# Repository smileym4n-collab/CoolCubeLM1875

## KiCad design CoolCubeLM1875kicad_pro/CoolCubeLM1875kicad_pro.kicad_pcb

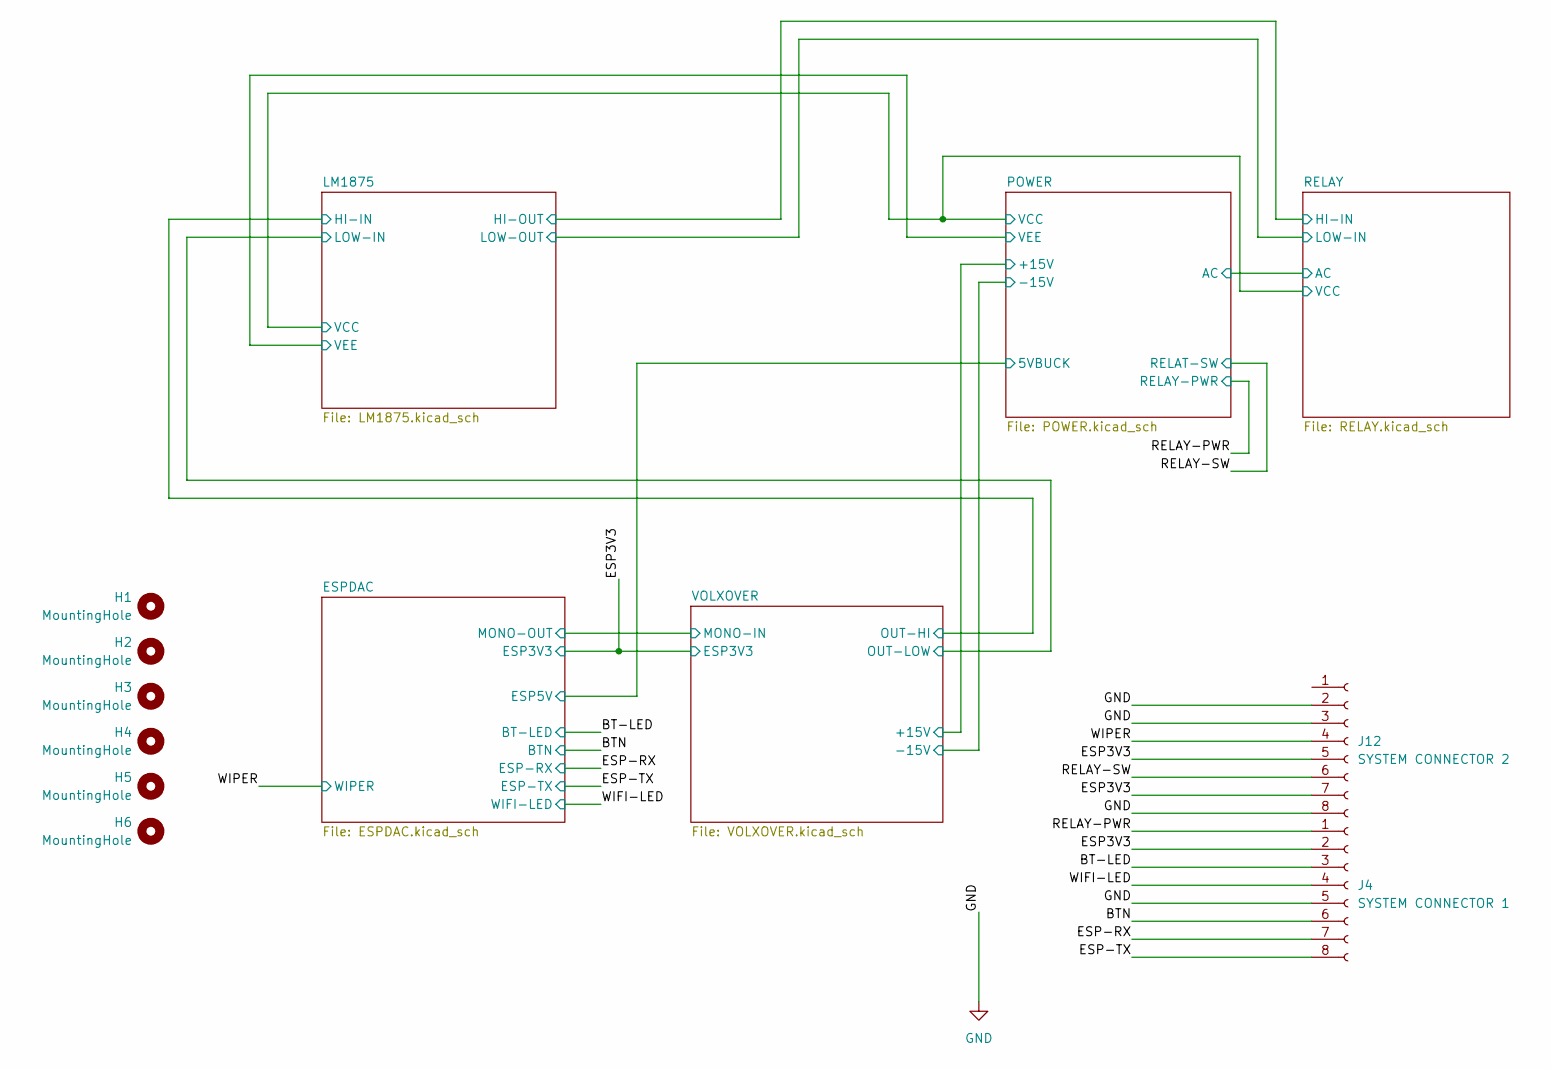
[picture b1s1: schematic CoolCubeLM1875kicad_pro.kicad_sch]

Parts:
H1, H2, H3, H4, H5, H6: MountingHole; MountingHole_4mm
J4: SYSTEM CONNECTOR 1; JST_XH_B8B-XH-A_1x08_P2.50mm_Vertical
J12: SYSTEM CONNECTOR 2; JST_XH_B8B-XH-A_1x08_P2.50mm_Vertical

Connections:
/BT-LED: J4.3; also elsewhere on the board
/BTN: J4.6; also elsewhere on the board
/ESP3V3: J4.2, J12.5, J12.7; also elsewhere on the board
/ESP-RX: J4.7; also elsewhere on the board
/ESP-TX: J4.8; also elsewhere on the board
/RELAY-PWR: J4.1; also elsewhere on the board
/RELAY-SW: J12.6; also elsewhere on the board
/WIFI-LED: J4.4; also elsewhere on the board
/WIPER: J12.4; also elsewhere on the board
GND: J4.5, J12.2, J12.3, J12.8; also elsewhere on the board

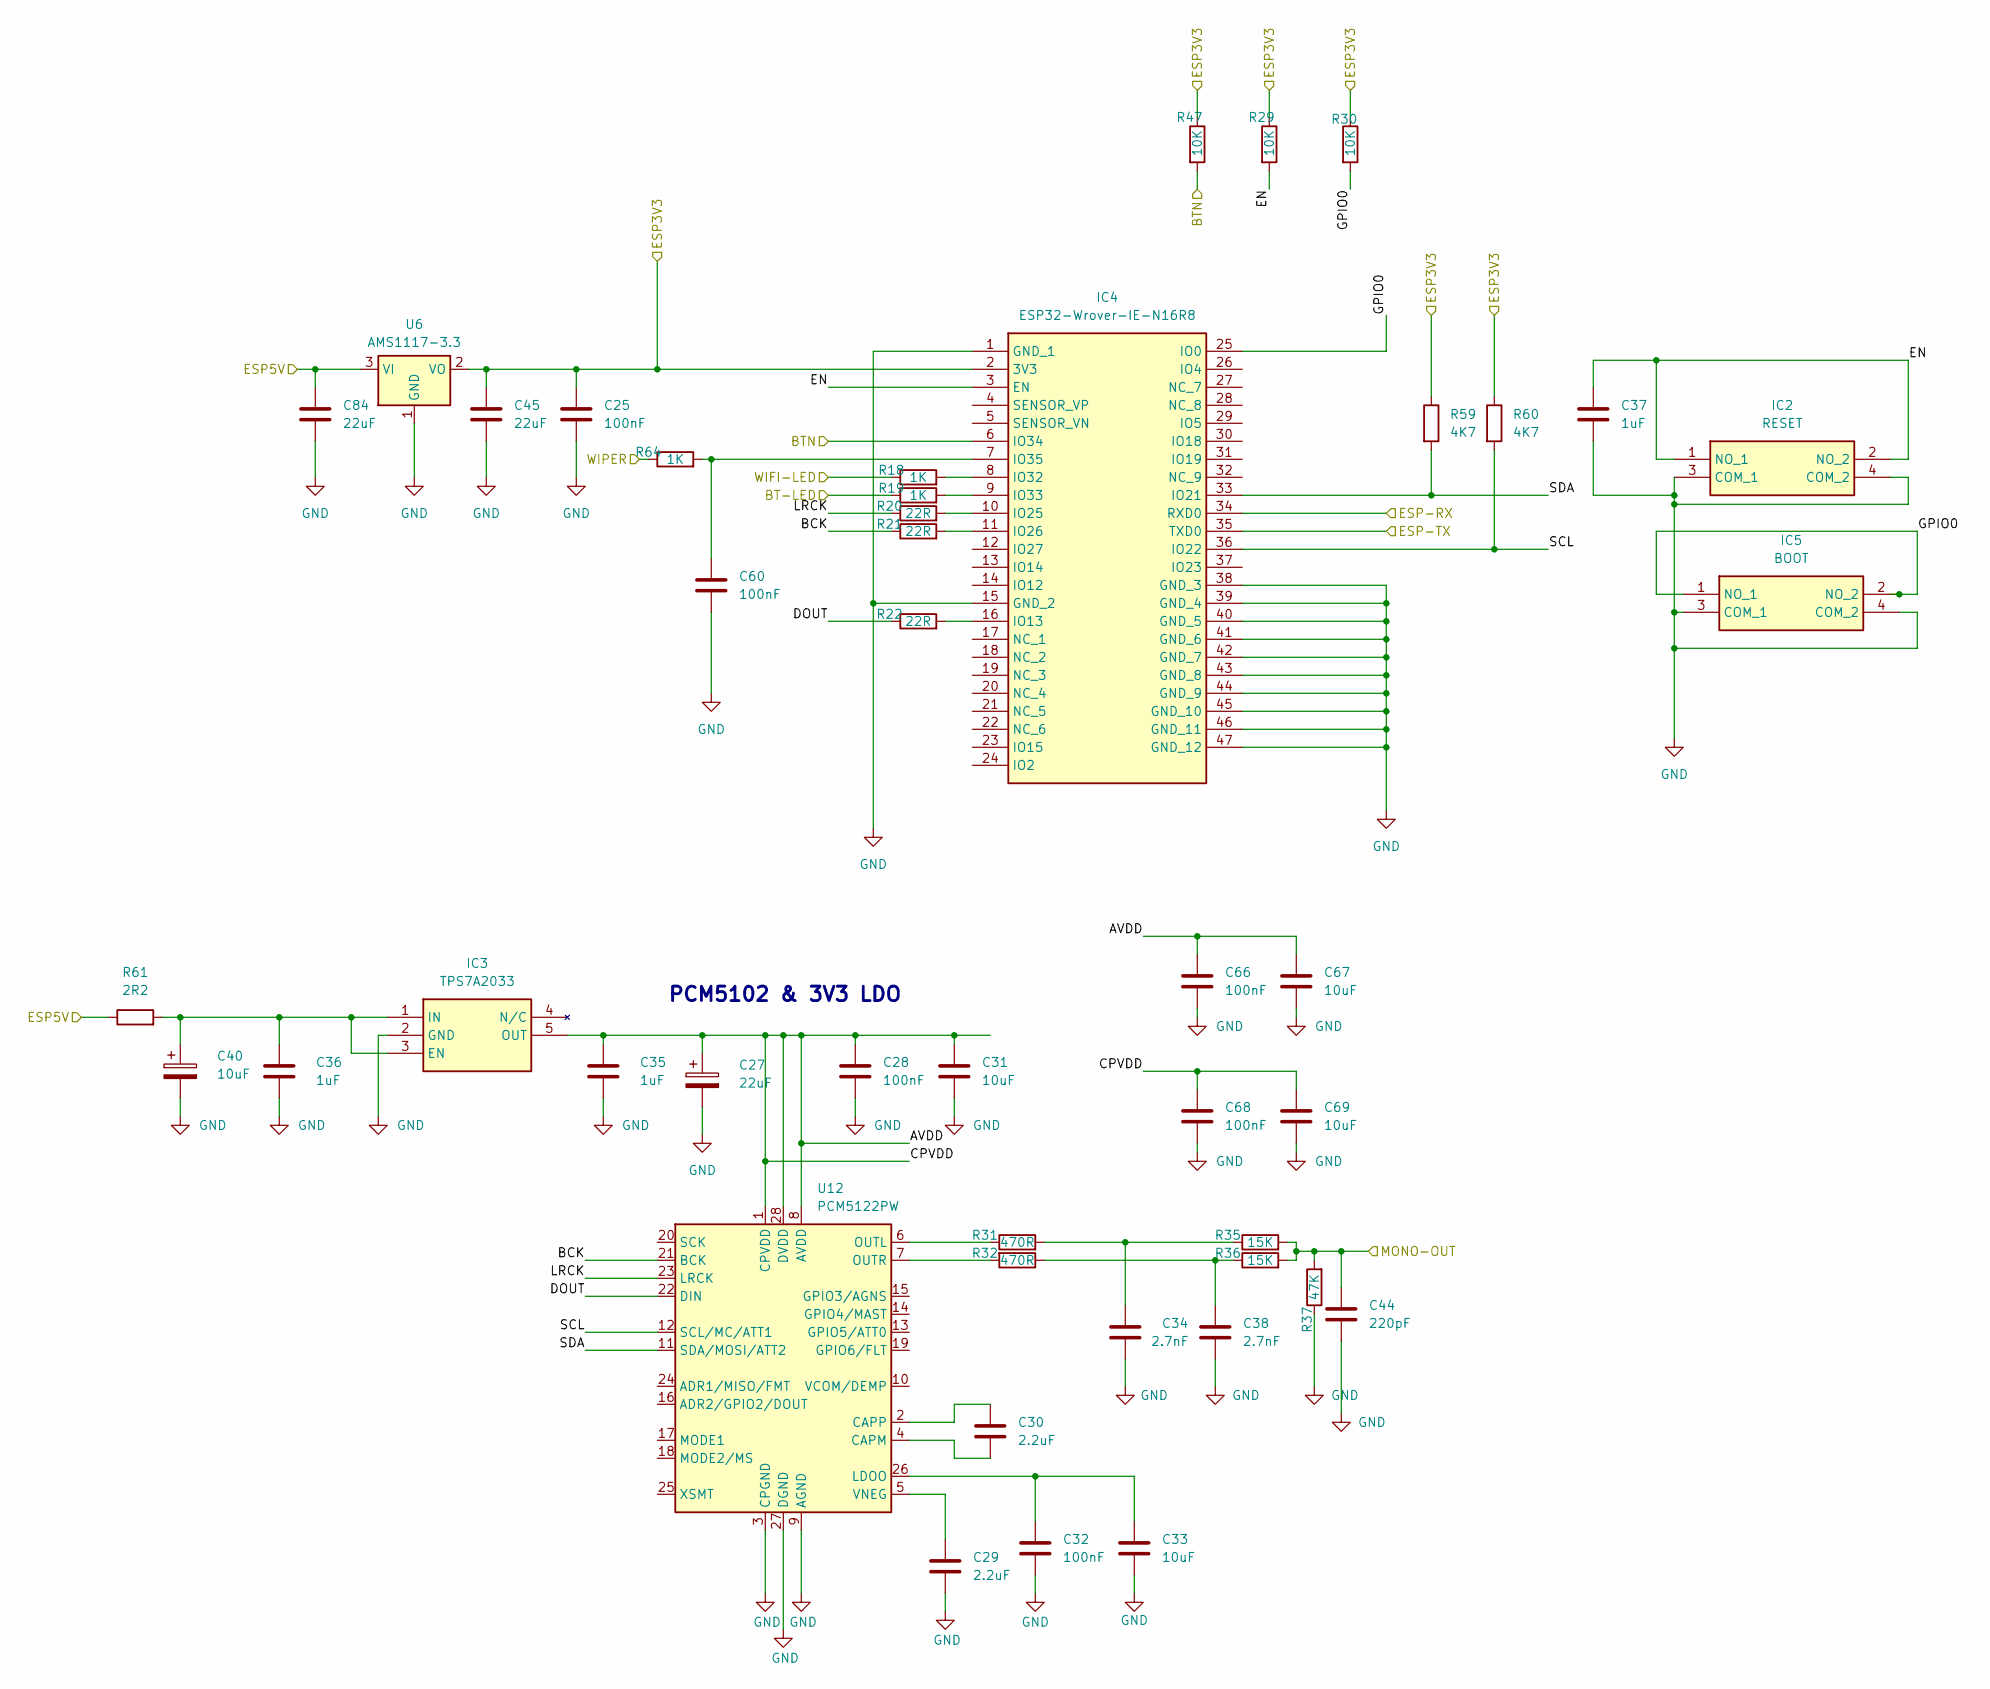
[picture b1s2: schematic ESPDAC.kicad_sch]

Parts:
C25, C28, C32, C60, C66, C68: 100nF; C_1206_3216Metric_Pad1.33x1.80mm_HandSolder
C27: 22uF; CP_Radial_D5.0mm_P2.50mm
C29, C30: 2.2uF; C_0805_2012Metric_Pad1.18x1.45mm_HandSolder
C31, C67, C69: 10uF; C_0805_2012Metric_Pad1.18x1.45mm_HandSolder
C33: 10uF; C_1206_3216Metric_Pad1.33x1.80mm_HandSolder
C34, C38: 2.7nF; C_0805_2012Metric_Pad1.18x1.45mm_HandSolder
C35, C36, C37: 1uF; C_1206_3216Metric_Pad1.33x1.80mm_HandSolder
C40: 10uF; CP_Radial_D4.0mm_P1.50mm
C44: 220pF; C_0603_1608Metric_Pad1.08x0.95mm_HandSolder
C45, C84: 22uF; C_0805_2012Metric_Pad1.18x1.45mm_HandSolder
IC2: RESET; TS026650BK100SCRD; Mouser Part Number 179-TS026650BK100SCR
IC3: TPS7A2033; SOT95P280X145-5N; Mouser Part Number 595-TPS7A2033PDBVR
IC4: ESP32-Wrover-IE-N16R8; ESP32-WROVER-IE-N16R8; Mouser Part Number 356-ESP32WRVIE2864UC
IC5: BOOT; TS026650BK100SCRD; Mouser Part Number 179-TS026650BK100SCR
R18, R19, R64: 1K; R_0805_2012Metric_Pad1.20x1.40mm_HandSolder
R20, R21, R22: 22R; R_0603_1608Metric_Pad0.98x0.95mm_HandSolder
R29, R30, R47: 10K; R_0603_1608Metric_Pad0.98x0.95mm_HandSolder
R31, R32: 470R; R_0805_2012Metric_Pad1.20x1.40mm_HandSolder
R35, R36: 15K; R_0805_2012Metric_Pad1.20x1.40mm_HandSolder
R37: 47K; R_0805_2012Metric_Pad1.20x1.40mm_HandSolder
R59, R60: 4K7; R_0805_2012Metric_Pad1.20x1.40mm_HandSolder
R61: 2R2; R_0805_2012Metric_Pad1.20x1.40mm_HandSolder
U6: AMS1117-3.3; SOT-223-3_TabPin2
U12: PCM5122PW; TSSOP-28_4.4x9.7mm_P0.65mm

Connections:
/BT-LED: R19.1; also elsewhere on the board
/BTN: IC4.6 (IO34), R47.2; also elsewhere on the board
/ESP3V3: C25.1, C45.1, IC4.2 (3V3), R29.1, R30.1, R47.1, R59.1, R60.1, U6.2 (VO); also elsewhere on the board
/ESP-RX: IC4.34 (RXD0); also elsewhere on the board
/ESP-TX: IC4.35 (TXD0); also elsewhere on the board
/ESPDAC/AVDD: C27.1, C28.1, C31.1, C35.1, C66.1, C67.1, C68.1, C69.1, IC3.5 (OUT), U12.1 (CPVDD), U12.8 (AVDD), U12.28 (DVDD)
/ESPDAC/BCK: R21.1, U12.21 (BCK)
/ESPDAC/DOUT: R22.1, U12.22 (DIN)
/ESPDAC/EN: C37.1, IC2.1 (NO_1), IC2.2 (NO_2), IC4.3 (EN), R29.2
/ESPDAC/ESP5V: C84.1, R61.1, U6.3 (VI); also elsewhere on the board
/ESPDAC/GPIO0: IC4.25 (IO0), IC5.1 (NO_1), IC5.2 (NO_2), R30.2
/ESPDAC/LRCK: R20.1, U12.23 (LRCK)
/ESPDAC/MONO-OUT: C44.1, R35.2, R36.2, R37.2; also elsewhere on the board
/ESPDAC/SCL: IC4.36 (IO22), R60.2, U12.12 (SCL/MC/ATT1)
/ESPDAC/SDA: IC4.33 (IO21), R59.2, U12.11 (SDA/MOSI/ATT2)
/WIFI-LED: R18.1; also elsewhere on the board
/WIPER: R64.1; also elsewhere on the board
GND: C25.2, C27.2, C28.2, C29.2, C31.2, C32.2, C33.2, C34.2, C35.2, C36.2, C37.2, C38.2, C40.2, C44.2, C45.2, C60.2, C66.2, C67.2, C68.2, C69.2, C84.2, IC2.3 (COM_1), IC2.4 (COM_2), IC3.2 (GND), IC4.1 (GND_1), IC4.15 (GND_2), IC4.38 (GND_3), IC4.39 (GND_4), IC4.40 (GND_5), IC4.41 (GND_6), IC4.42 (GND_7), IC4.43 (GND_8), IC4.44 (GND_9), IC4.45 (GND_10), IC4.46 (GND_11), IC4.47 (GND_12), IC5.3 (COM_1), IC5.4 (COM_2), R37.1, U6.1 (GND), U12.3 (CPGND), U12.9 (AGND), U12.27 (DGND); also elsewhere on the board
unnamed: C34.1, R31.2, R35.1
unnamed: C38.1, R32.1, R36.1
unnamed: C36.1, C40.1, IC3.1 (IN), IC3.3 (EN), R61.2
unnamed: IC4.16 (IO13), R22.2
unnamed: IC4.10 (IO25), R20.2
unnamed: IC4.11 (IO26), R21.2
unnamed: IC4.8 (IO32), R18.2
unnamed: IC4.9 (IO33), R19.2
unnamed: C60.1, IC4.7 (IO35), R64.2
unnamed: C30.2, U12.4 (CAPM)
unnamed: C30.1, U12.2 (CAPP)
unnamed: C32.1, C33.1, U12.26 (LDOO)
unnamed: R31.1, U12.6 (OUTL)
unnamed: R32.2, U12.7 (OUTR)
unnamed: C29.1, U12.5 (VNEG)

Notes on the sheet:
PCM5102 & 3V3 LDO

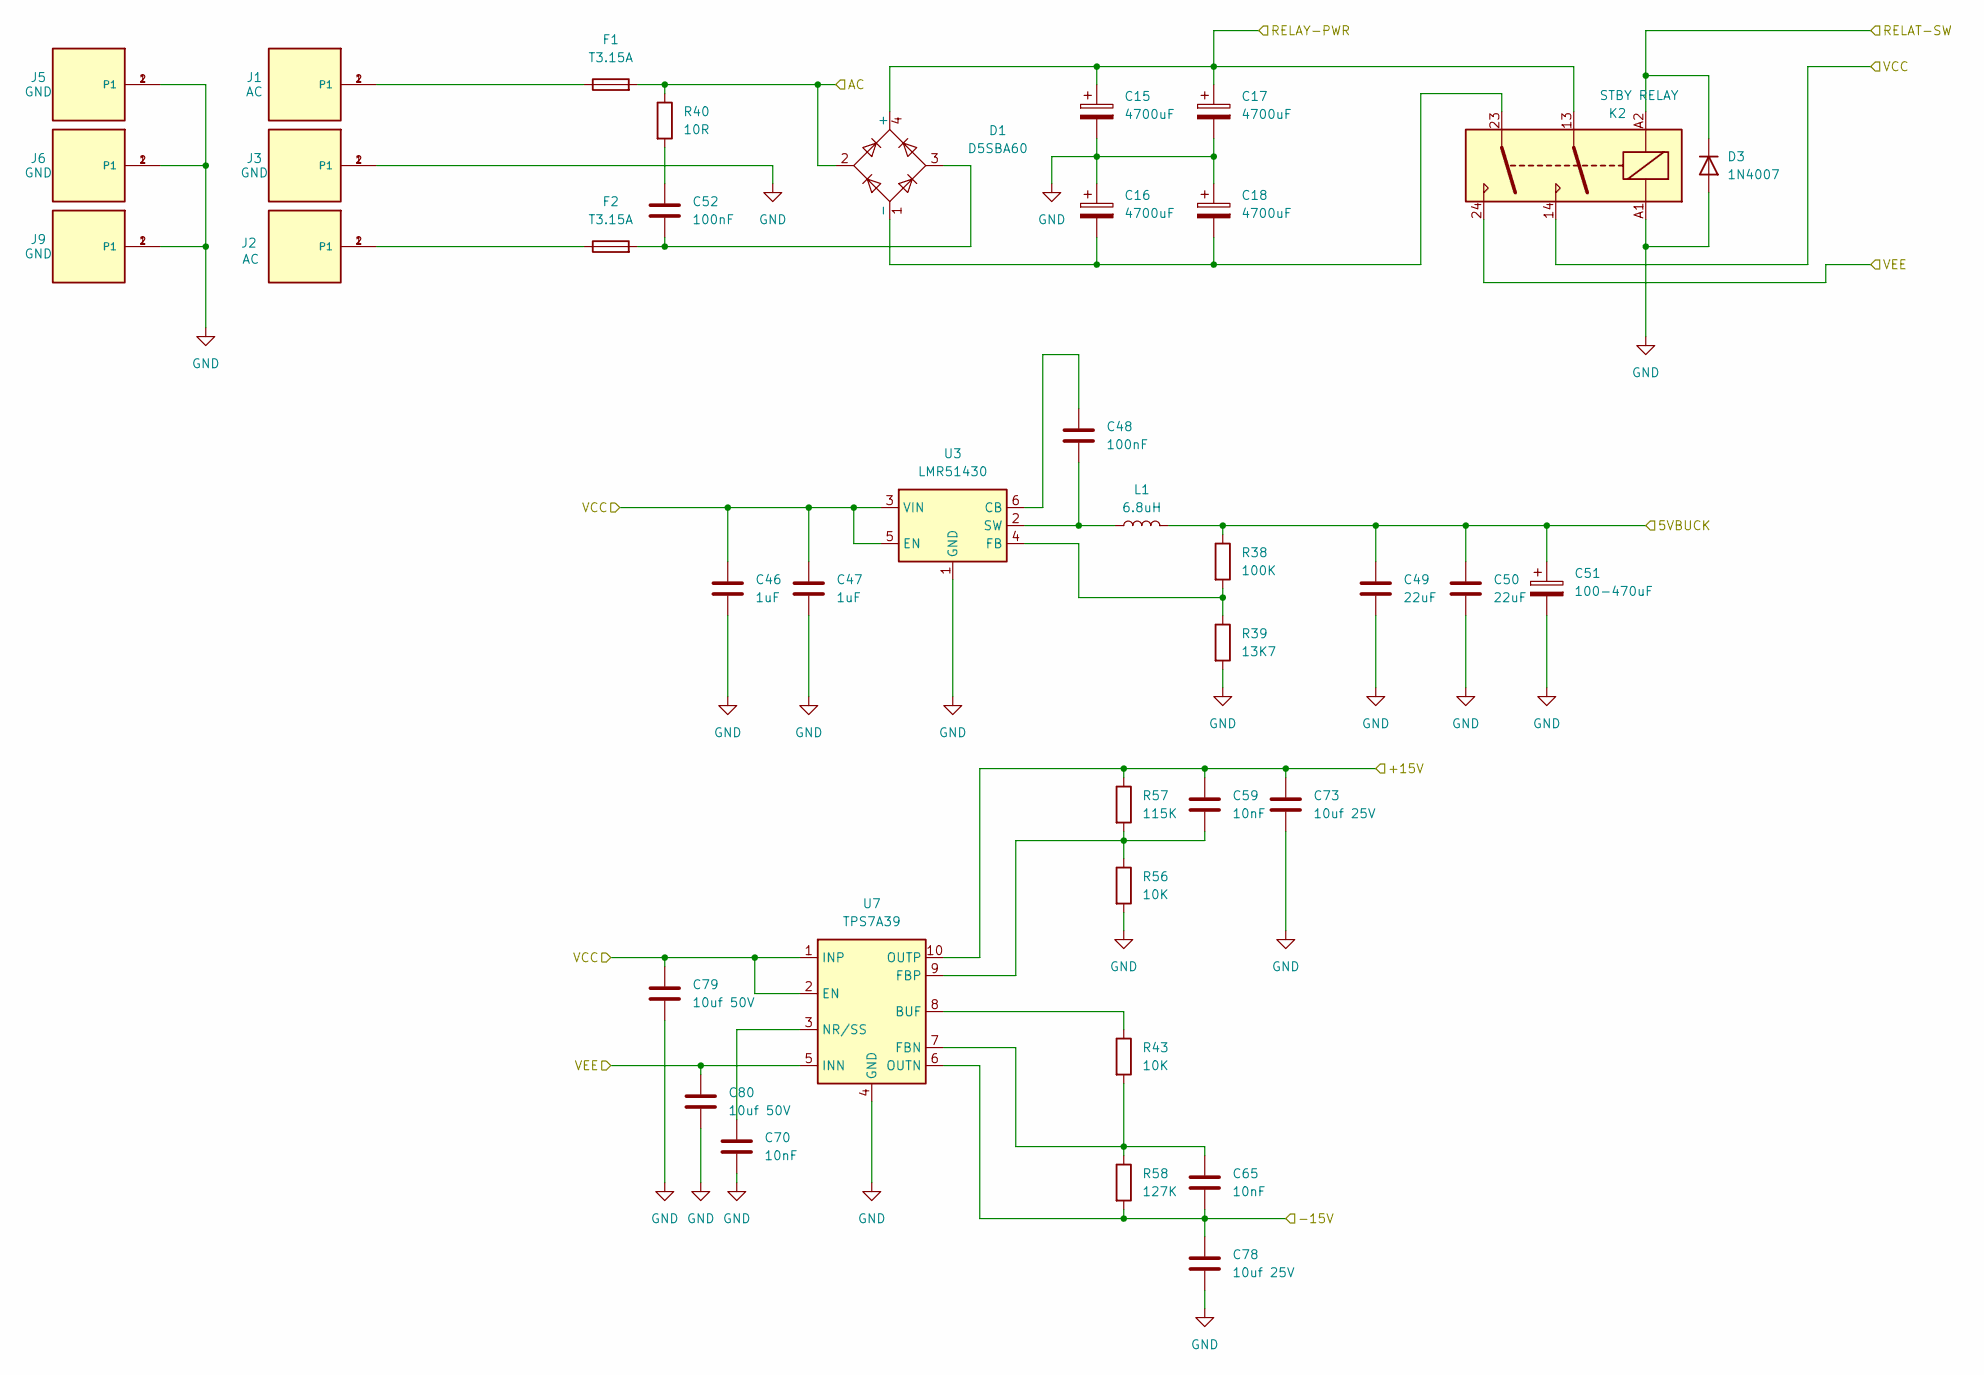
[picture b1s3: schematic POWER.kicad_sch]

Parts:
C15, C16, C17, C18: 4700uF; CP_Radial_D22.0mm_P10.00mm_SnapIn
C46, C47: 1uF; C_1206_3216Metric_Pad1.33x1.80mm_HandSolder
C48: 100nF; C_1206_3216Metric_Pad1.33x1.80mm_HandSolder
C49, C50: 22uF; C_1206_3216Metric_Pad1.33x1.80mm_HandSolder
C51: 100-470uF; CP_Radial_D8.0mm_P3.50mm
C52: 100nF; C_Rect_L18.0mm_W5.0mm_P15.00mm_FKS3_FKP3
C59, C65, C70: 10nF; C_0805_2012Metric_Pad1.18x1.45mm_HandSolder
C73, C78: 10uf 25V; C_1206_3216Metric_Pad1.33x1.80mm_HandSolder
C79, C80: 10uf 50V; C_1206_3216Metric_Pad1.33x1.80mm_HandSolder
D1: D5SBA60; Diode_Bridge_32.0x5.6x17.0mm_P10.0mm_P7.5mm
D3: 1N4007; D_DO-41_SOD81_P10.16mm_Horizontal
F1, F2: T3.15A; Fuseholder_Cylinder-5x20mm_Schurter_0031_8201_Horizontal_Op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
J1, J2: AC; TE_62409-1; PART_DESCRIPTION CONN QC TAB 0.250 SOLDER
J3, J5, J6, J9: GND; TE_62409-1; PART_DESCRIPTION CONN QC TAB 0.250 SOLDER
K2: STBY RELAY; Relay_DPST_Omron_G2RL-2A
L1: 6.8uH; SRP6030WA-6R8M
R38: 100K; R_0805_2012Metric_Pad1.20x1.40mm_HandSolder
R39: 13K7; R_0805_2012Metric_Pad1.20x1.40mm_HandSolder
R40: 10R; R_Axial_DIN0617_L17.0mm_D6.0mm_P20.32mm_Horizontal
R43, R56: 10K; R_0805_2012Metric_Pad1.20x1.40mm_HandSolder
R57: 115K; R_0805_2012Metric_Pad1.20x1.40mm_HandSolder
R58: 127K; R_0805_2012Metric_Pad1.20x1.40mm_HandSolder
U3: LMR51430; SOT-23-6_Handsoldering
U7: TPS7A39; Texas_S-PVSON-N10_ThermalVias

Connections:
/ESPDAC/ESP5V: C49.1, C50.1, C51.1, L1.2, R38.1; also elsewhere on the board
/LM1875/VCC: C46.1, C47.1, C79.1, K2.14, U3.3 (VIN), U3.5 (EN), U7.1 (INP), U7.2 (EN); also elsewhere on the board
/LM1875/VEE: C80.1, K2.24, U7.5 (INN); also elsewhere on the board
/POWER/+15V: C59.1, C73.1, R57.1, U7.10 (OUTP); also elsewhere on the board
/POWER/-15V: C65.2, C78.1, R58.2, U7.6 (OUTN); also elsewhere on the board
/POWER/AC: D1.2, F1.2, R40.1; also elsewhere on the board
/RELAY-PWR: C15.1, C17.1, D1.4 (+), K2.13; also elsewhere on the board
/RELAY-SW: D3.1 (K), K2.A2; also elsewhere on the board
GND: C15.2, C16.1, C17.2, C18.1, C46.2, C47.2, C49.2, C50.2, C51.2, C70.2, C73.2, C78.2, C79.2, C80.2, D3.2 (A), J3.1, J3.2 (P1), J5.1, J5.2 (P1), J6.1, J6.2 (P1), J9.1, J9.2 (P1), K2.A1, R39.2, R56.2, U3.1 (GND), U7.4 (GND), U7.11 (GND); also elsewhere on the board
unnamed: C52.1, R40.2
unnamed: C52.2, D1.3, F2.2
unnamed: C16.2, C18.2, D1.1 (-), K2.23
unnamed: F1.1, J1.1, J1.2 (P1)
unnamed: F2.1, J2.1, J2.2 (P1)
unnamed: C48.1, U3.6 (CB)
unnamed: R38.2, R39.1, U3.4 (FB)
unnamed: C48.2, L1.1, U3.2 (SW)
unnamed: R43.1, U7.8 (BUF)
unnamed: C65.1, R43.2, R58.1, U7.7 (FBN)
unnamed: C59.2, R56.1, R57.2, U7.9 (FBP)
unnamed: C70.1, U7.3 (NR/SS)

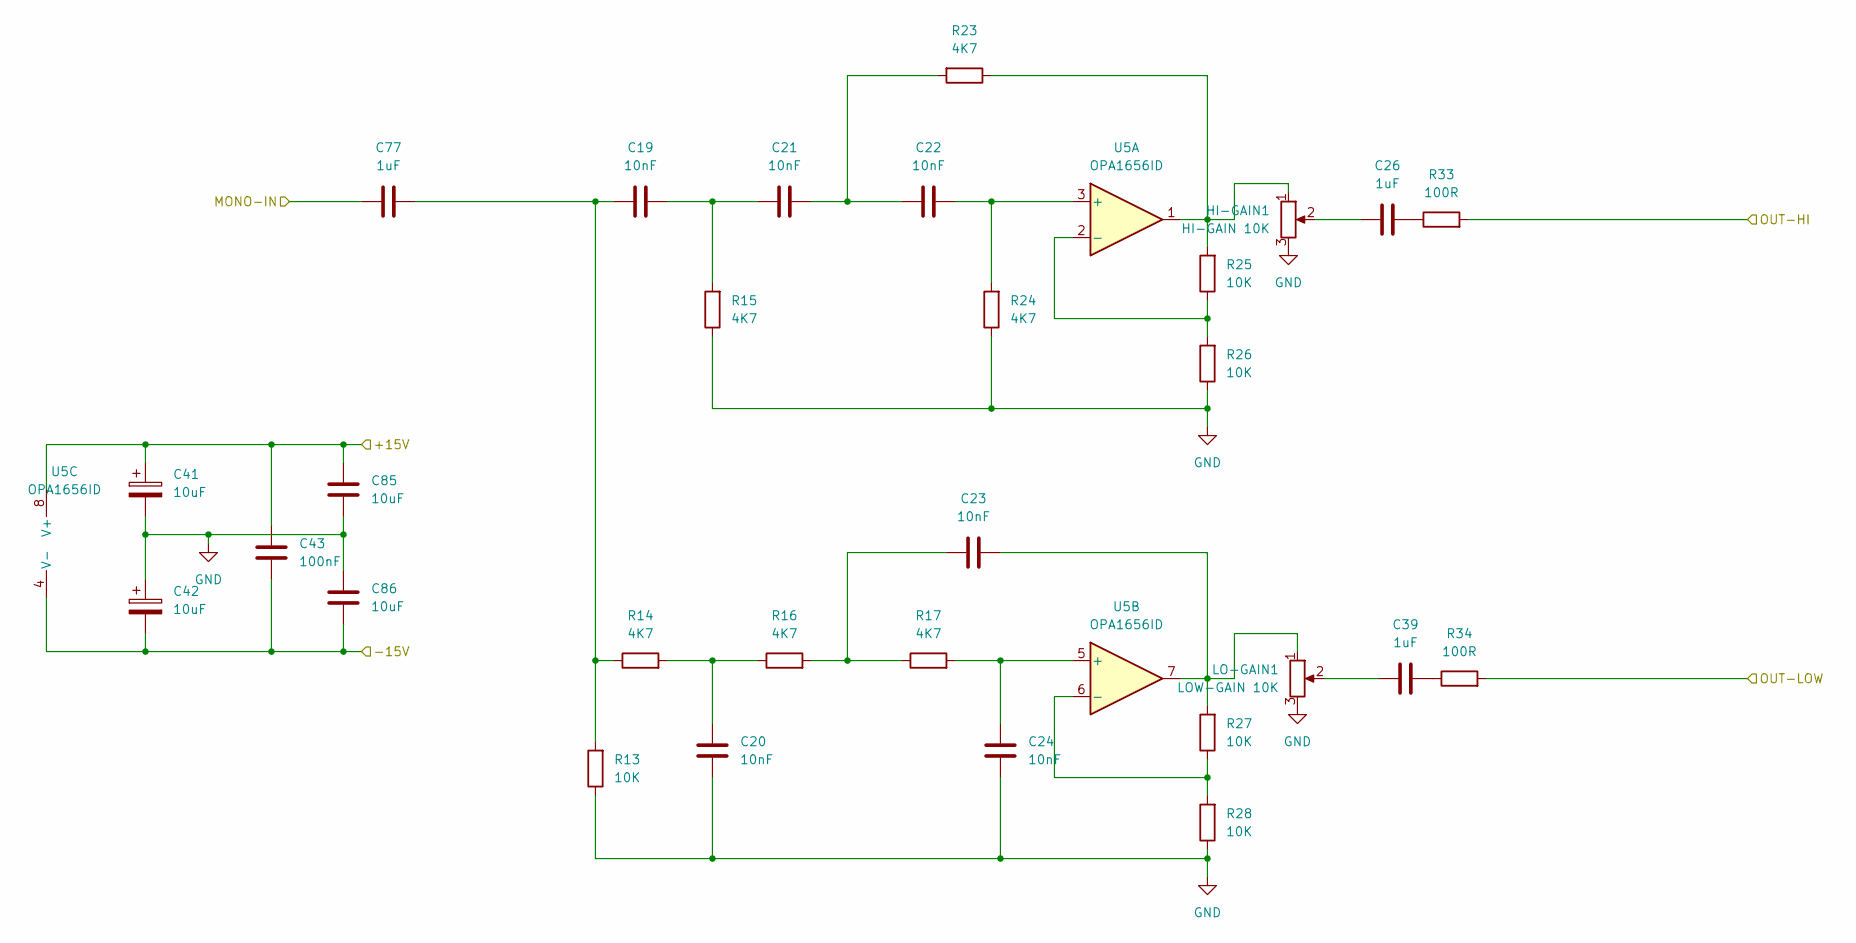
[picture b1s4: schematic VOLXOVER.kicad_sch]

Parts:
C19, C20, C21, C22, C23, C24: 10nF; C_0805_2012Metric_Pad1.18x1.45mm_HandSolder
C26, C39, C77: 1uF; C_Rect_L7.2mm_W5.5mm_P5.00mm_FKS2_FKP2_MKS2_MKP2
C41, C42: 10uF; CP_Radial_D5.0mm_P2.50mm
C43: 100nF; C_1206_3216Metric_Pad1.33x1.80mm_HandSolder
C85, C86: 10uF; C_1206_3216Metric_Pad1.33x1.80mm_HandSolder
HI-GAIN1: HI-GAIN 10K; Potentiometer_Vishay_T93YA_Vertical
LO-GAIN1: LOW-GAIN 10K; Potentiometer_Vishay_T93YA_Vertical
R13, R25, R26, R27, R28: 10K; R_0805_2012Metric_Pad1.20x1.40mm_HandSolder
R14, R15, R16, R17, R23, R24: 4K7; R_0805_2012Metric_Pad1.20x1.40mm_HandSolder
R33, R34: 100R; R_0805_2012Metric_Pad1.20x1.40mm_HandSolder
U5: OPA1656ID; SOIC-8_3.9x4.9mm_P1.27mm

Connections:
/ESPDAC/MONO-OUT: C77.1; also elsewhere on the board
/LM1875/HI-IN: R33.2; also elsewhere on the board
/LM1875/LOW-IN: R34.2; also elsewhere on the board
/POWER/+15V: C41.1, C43.1, C85.1, U5.8 (V+); also elsewhere on the board
/POWER/-15V: C42.2, C43.2, C86.2, U5.4 (V-); also elsewhere on the board
GND: C20.1, C24.1, C41.2, C42.1, C85.2, C86.1, HI-GAIN1.3, LO-GAIN1.3, R13.1, R15.1, R24.1, R26.1, R28.1; also elsewhere on the board
unnamed: C19.1, C77.2, R13.2, R14.1
unnamed: C19.2, C21.1, R15.2
unnamed: C20.2, R14.2, R16.1
unnamed: C21.2, C22.1, R23.2
unnamed: C23.1, R16.2, R17.1
unnamed: C23.2, LO-GAIN1.1, R27.2, U5.7
unnamed: C26.1, HI-GAIN1.2
unnamed: C26.2, R33.1
unnamed: C39.1, LO-GAIN1.2
unnamed: C39.2, R34.1
unnamed: HI-GAIN1.1, R23.1, R25.2, U5.1
unnamed: C22.2, R24.2, U5.3 (+)
unnamed: R25.1, R26.2, U5.2 (-)
unnamed: C24.2, R17.2, U5.5 (+)
unnamed: R27.1, R28.2, U5.6 (-)

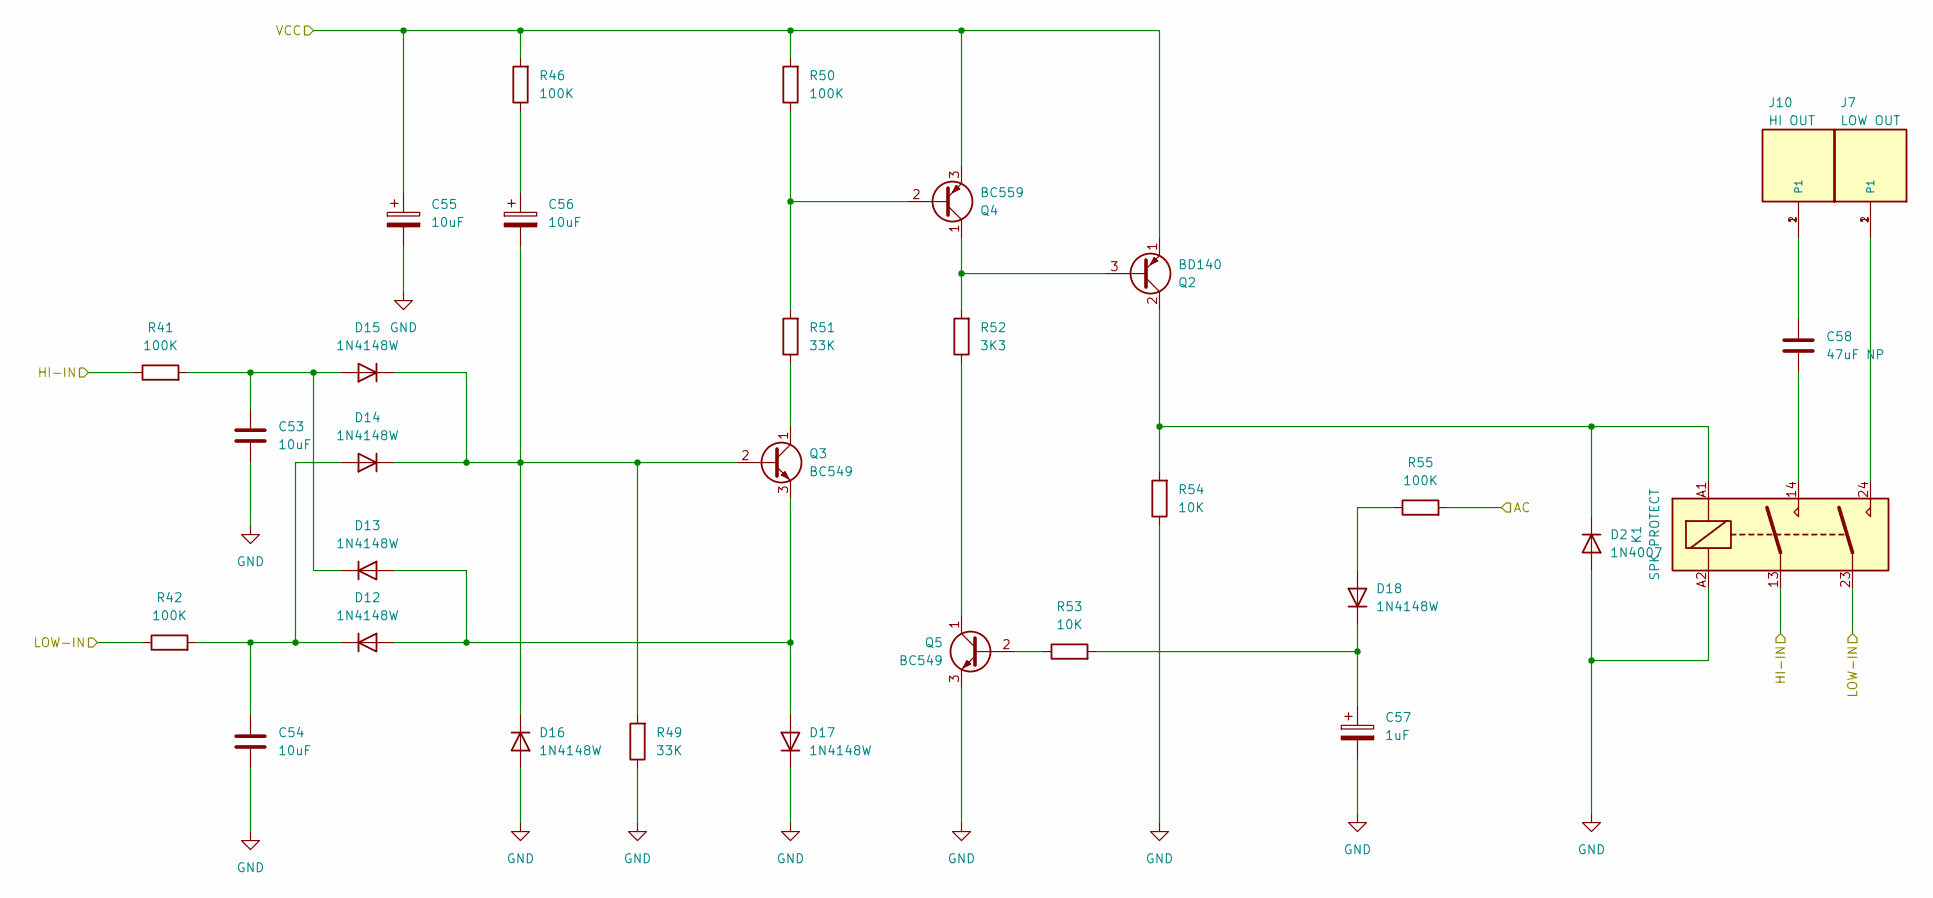
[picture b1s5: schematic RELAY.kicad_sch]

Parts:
C53, C54: 10uF; C_Radial_D6.3mm_H7.0mm_P2.50mm
C55, C56: 10uF; CP_Radial_D5.0mm_P2.00mm
C57: 1uF; CP_Radial_D5.0mm_P2.00mm
C58: 47uF NP; C_Radial_D10.0mm_H20.0mm_P5.00mm
D2: 1N4007; D_DO-41_SOD81_P10.16mm_Horizontal
D12, D13, D14, D15, D16, D17, D18: 1N4148W; D_SOD-123
J7: LOW OUT; TE_62409-1; PART_DESCRIPTION CONN QC TAB 0.250 SOLDER
J10: HI OUT; TE_62409-1; PART_DESCRIPTION CONN QC TAB 0.250 SOLDER
K1: SPK PROTECT; Relay_DPST_Omron_G2RL-2A
Q2: BD140; TO-126-3_Vertical
Q3, Q5: BC549; TO-92L_Inline_Wide
Q4: BC559; TO-92L_Inline_Wide
R41, R42, R46, R50, R55: 100K; R_0805_2012Metric_Pad1.20x1.40mm_HandSolder
R49, R51: 33K; R_0805_2012Metric_Pad1.20x1.40mm_HandSolder
R52: 3K3; R_0805_2012Metric_Pad1.20x1.40mm_HandSolder
R53, R54: 10K; R_0805_2012Metric_Pad1.20x1.40mm_HandSolder

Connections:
/LM1875/HI-OUT: K1.13, R41.1; also elsewhere on the board
/LM1875/LOW-OUT: K1.23, R42.1; also elsewhere on the board
/LM1875/VCC: C55.1, Q2.1 (E), Q4.3 (E), R46.2, R50.2; also elsewhere on the board
/POWER/AC: R55.2; also elsewhere on the board
GND: C53.1, C54.1, C55.2, C57.2, D2.2 (A), D16.2 (A), D17.1 (K), K1.A2, Q5.3 (E), R49.1, R54.1; also elsewhere on the board
unnamed: C56.1, R46.1
unnamed: C58.1, J10.1, J10.2 (P1)
unnamed: C58.2, K1.14
unnamed: D2.1 (K), K1.A1, Q2.2 (C), R54.2
unnamed: D12.2 (A), D13.2 (A), D17.2 (A), Q3.3 (E)
unnamed: C54.2, D12.1 (K), D14.2 (A), R42.2
unnamed: C53.2, D13.1 (K), D15.2 (A), R41.2
unnamed: C56.2, D14.1 (K), D15.1 (K), D16.1 (K), Q3.2 (B), R49.2
unnamed: D18.2 (A), R55.1
unnamed: C57.1, D18.1 (K), R53.2
unnamed: J7.1, J7.2 (P1), K1.24
unnamed: Q2.3 (B), Q4.1 (C), R52.2
unnamed: Q3.1 (C), R51.1
unnamed: Q4.2 (B), R50.1, R51.2
unnamed: Q5.2 (B), R53.1
unnamed: Q5.1 (C), R52.1

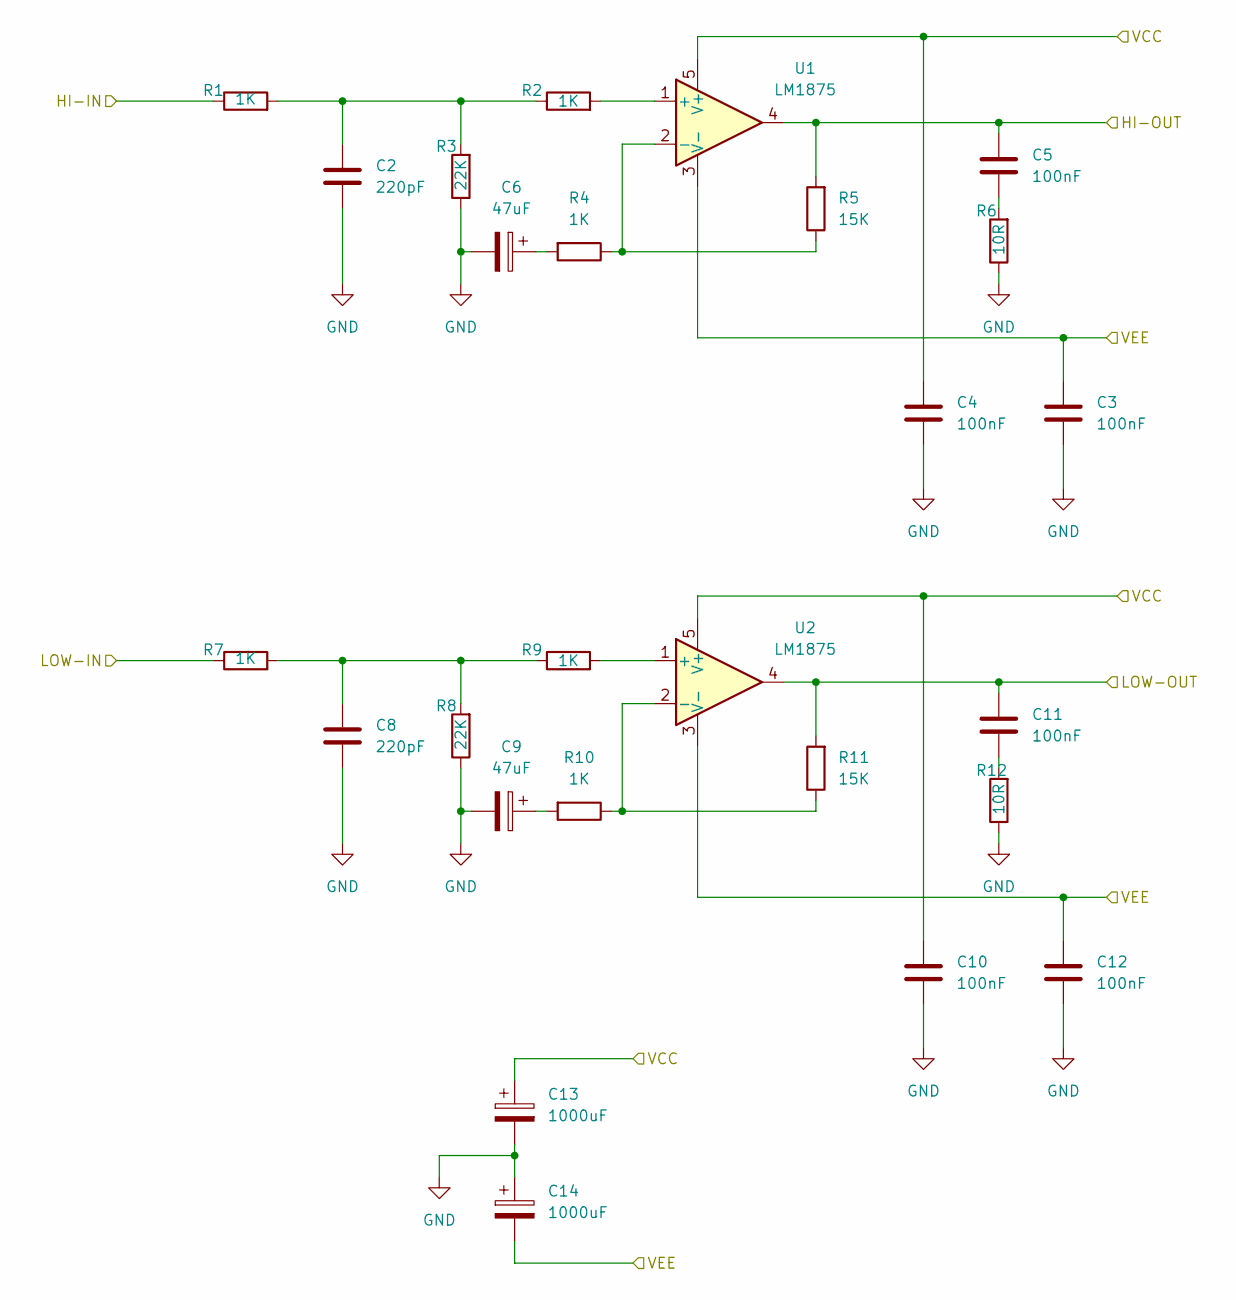
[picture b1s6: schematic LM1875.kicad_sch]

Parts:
C2, C8: 220pF; C_0805_2012Metric_Pad1.18x1.45mm_HandSolder
C3, C4, C10, C12: 100nF; C_1206_3216Metric_Pad1.33x1.80mm_HandSolder
C5, C11: 100nF; C_Rect_L7.2mm_W2.5mm_P5.00mm_FKS2_FKP2_MKS2_MKP2
C6, C9: 47uF; CP_Radial_D6.3mm_P2.50mm
C13, C14: 1000uF; CP_Radial_D12.5mm_P5.00mm
R1, R2, R4, R7, R9, R10: 1K; R_0805_2012Metric_Pad1.20x1.40mm_HandSolder
R3, R8: 22K; R_0805_2012Metric_Pad1.20x1.40mm_HandSolder
R5, R11: 15K; R_0805_2012Metric_Pad1.20x1.40mm_HandSolder
R6, R12: 10R; R_Axial_DIN0309_L9.0mm_D3.2mm_P12.70mm_Horizontal
U1, U2: LM1875; TO-220-5_P3.4x3.7mm_StaggerOdd_Lead3.8mm_Vertical

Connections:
/LM1875/HI-IN: R1.1; also elsewhere on the board
/LM1875/HI-OUT: C5.1, R5.2, U1.4; also elsewhere on the board
/LM1875/LOW-IN: R7.1; also elsewhere on the board
/LM1875/LOW-OUT: C11.1, R11.2, U2.4; also elsewhere on the board
/LM1875/VCC: C4.1, C10.1, C13.1, U1.5 (V+), U2.5 (V+); also elsewhere on the board
/LM1875/VEE: C3.1, C12.1, C14.2, U1.3 (V-), U2.3 (V-); also elsewhere on the board
GND: C2.2, C3.2, C4.2, C6.2, C8.2, C9.2, C10.2, C12.2, C13.2, C14.1, R3.1, R6.1, R8.1, R12.1; also elsewhere on the board
unnamed: C2.1, R1.2, R2.1, R3.2
unnamed: C5.2, R6.2
unnamed: C6.1, R4.2
unnamed: C8.1, R7.2, R8.2, R9.1
unnamed: C9.1, R10.2
unnamed: C11.2, R12.2
unnamed: R2.2, U1.1 (+)
unnamed: R4.1, R5.1, U1.2 (-)
unnamed: R9.2, U2.1 (+)
unnamed: R10.1, R11.1, U2.2 (-)

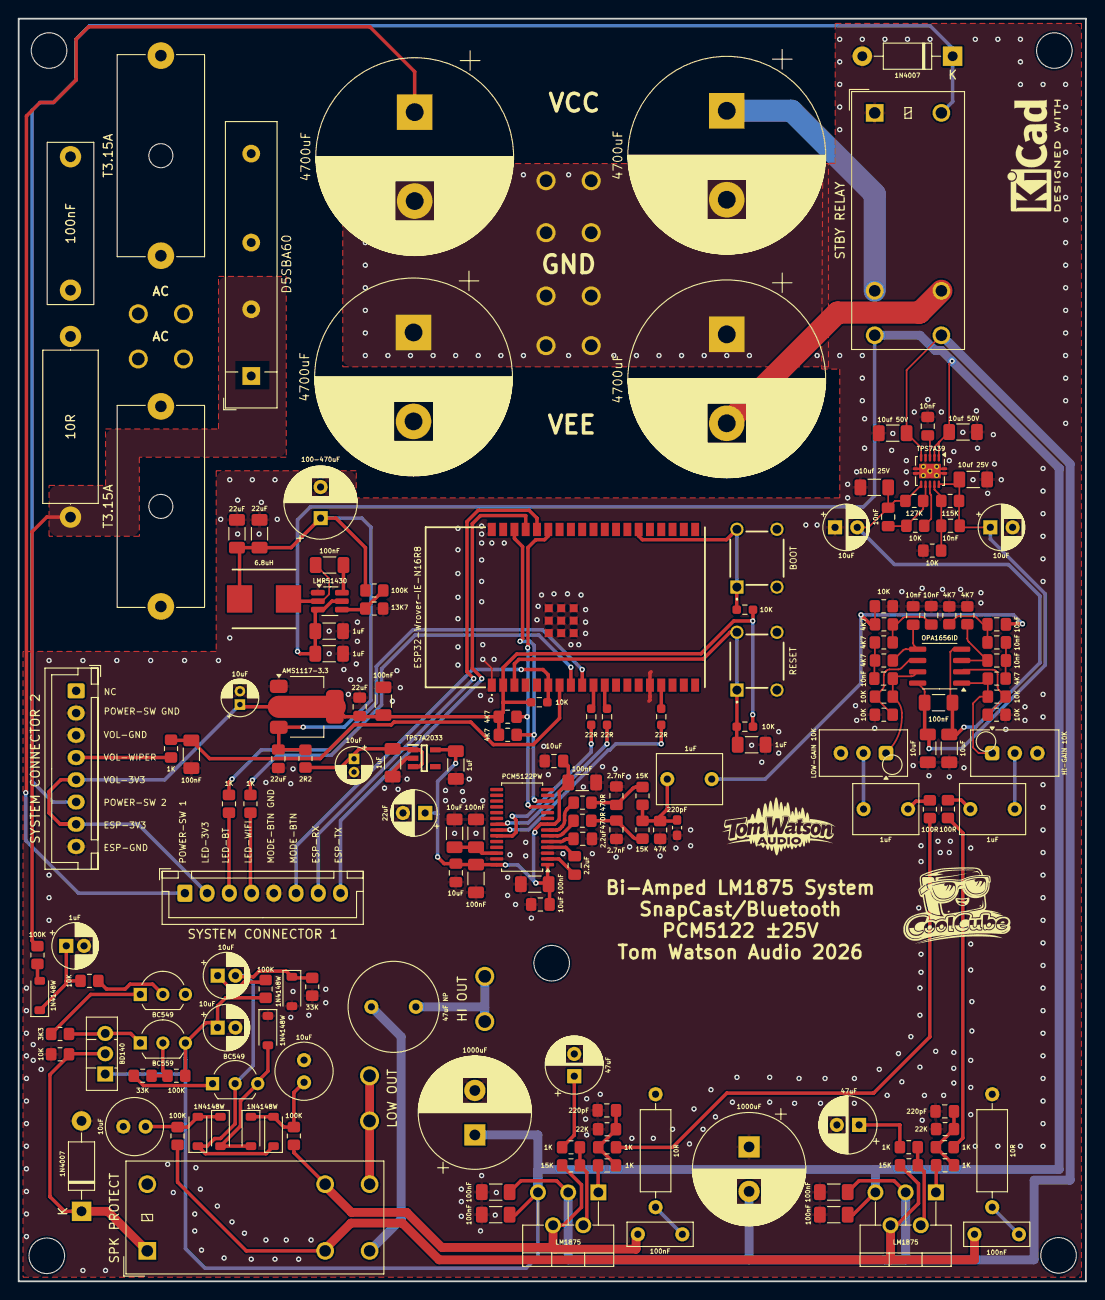
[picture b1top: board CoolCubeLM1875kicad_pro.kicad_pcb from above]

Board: 2 copper layers, 120.0 x 142.0 mm, 180 parts (0 on the bottom side), 97 nets.

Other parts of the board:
C71: 10uF; CP_Radial_D4.0mm_P1.50mm

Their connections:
/ESP3V3: C71.1; also elsewhere on the board
GND: C71.2; also elsewhere on the board
